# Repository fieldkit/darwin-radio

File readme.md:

DARWIN-RADIO

Experimental development repo for next-generation FieldKit hardware.

-- This hardware is experimental and still under development, the designs may contain errors. --

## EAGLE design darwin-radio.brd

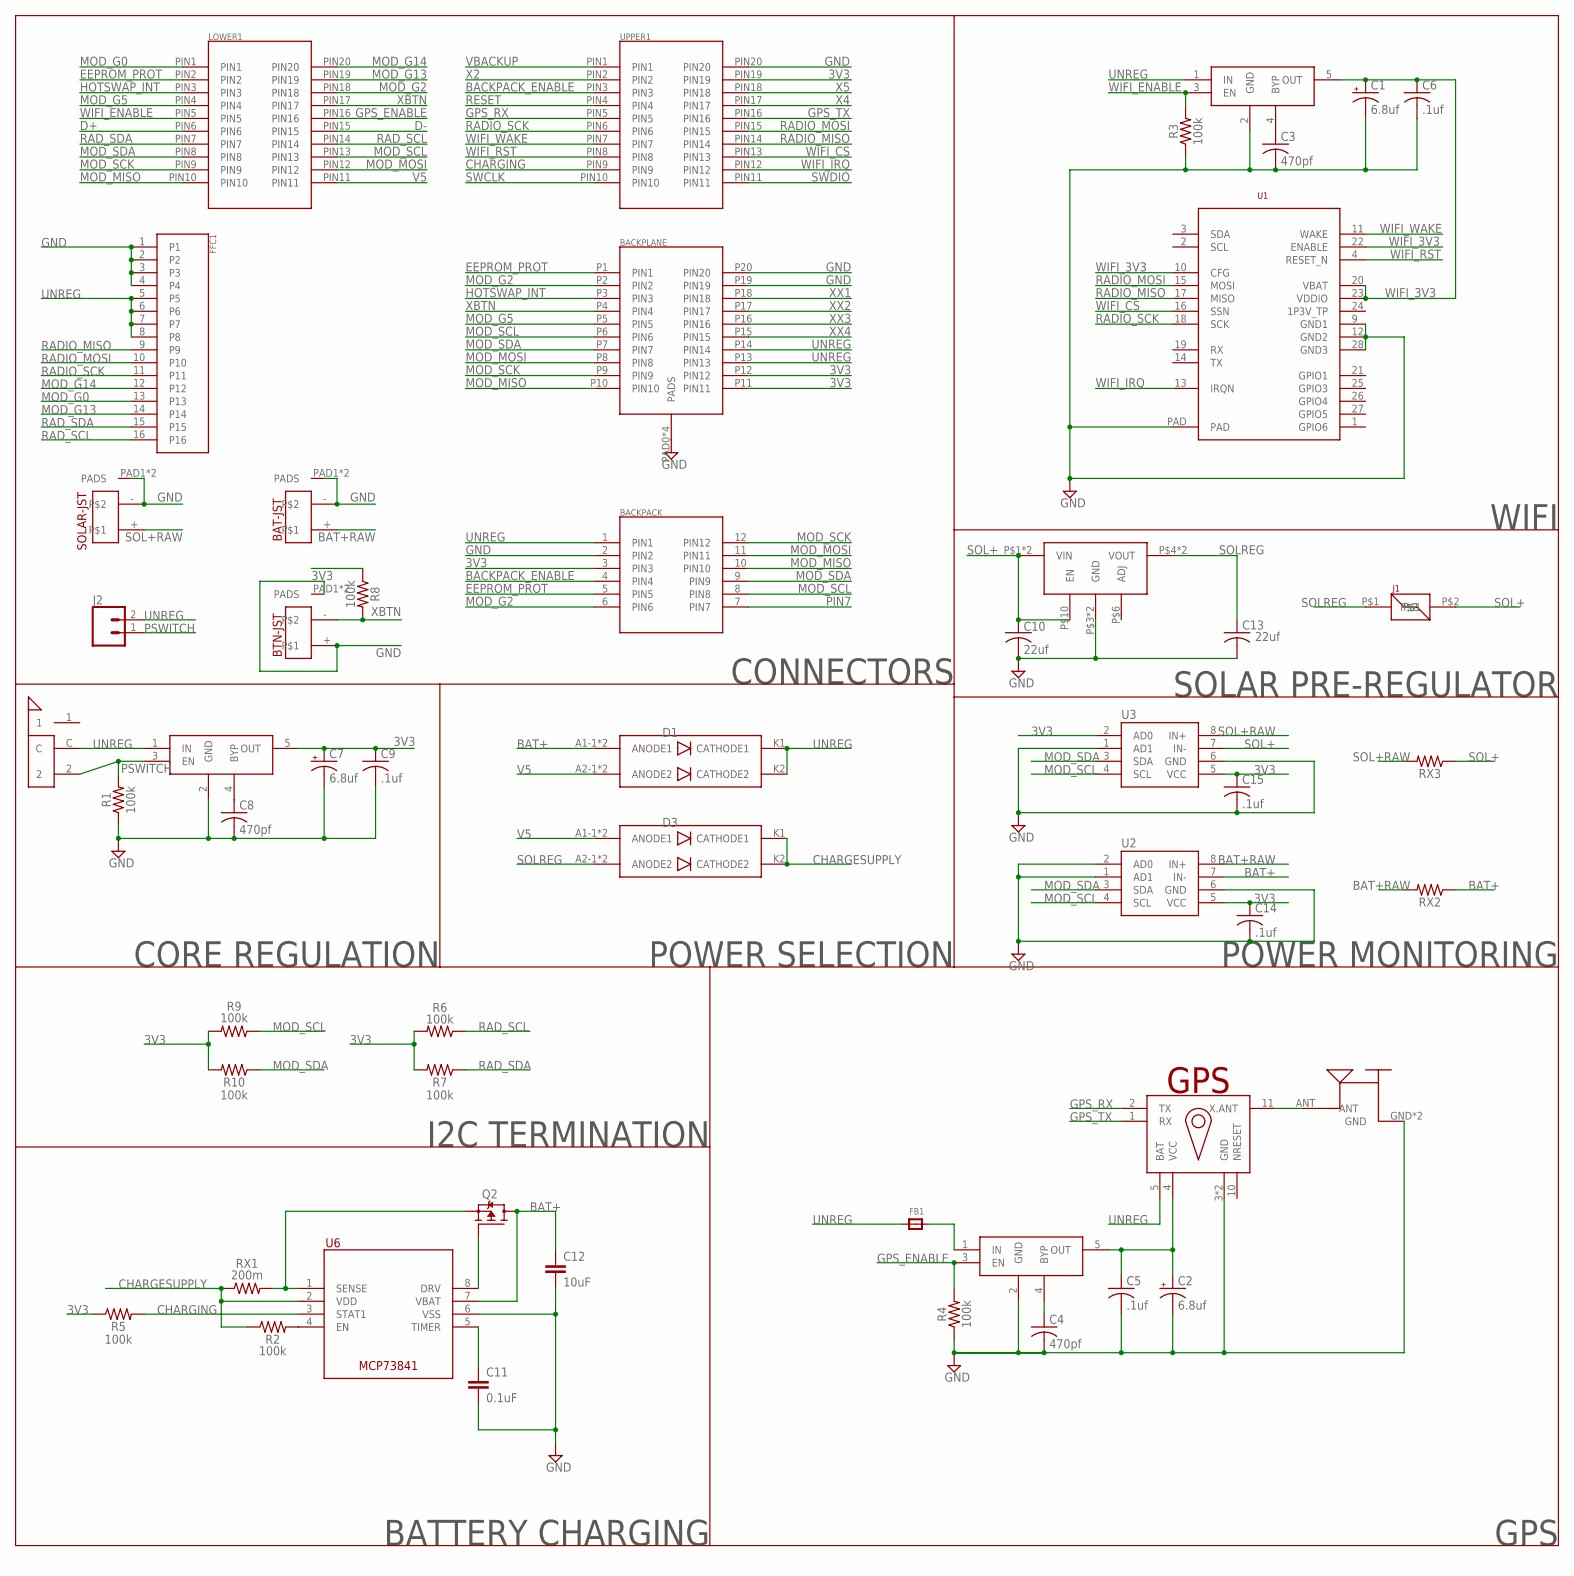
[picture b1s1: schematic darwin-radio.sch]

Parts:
BACKPACK: 2X6-HEADERSDS; 12PH
BACKPLANE: M55-6102042R
BAT-JST: B2B-PH-SM4-TB
BTN-JST: B2B-PH-SM4-TB
C1, C2, C7: 6.8uf; A/3216-18R
C3, C4, C8: 470pf; C0603K
C5, C6, C9, C14, C15: .1uf; C0603K
C10, C13: 22uf; C0603K
C11: 0.1uF; 0603
C12: 10uF; 0603
D1, D3: V10KL45DUHM3/H
FB1: FERRITE0805; 0805
FFC1: 505110-1692
J1: S1911-46R
J2: CONN_02LOCK_LONGPADS; 1X02_LOCK_LONGPADS
LOWER1: MOLEX-15-91-2200; 20PH
Q2: NDS8434; SO08-IRF
R1, R2, R3, R4, R5, R6, R7, R8, R9, R10: 100k; 0603
REG1: V78E06-1000-SMT-TR
RX1: 200m; R2512
RX2, RX3: 100M; R2512
SOLAR-JST: B2B-PH-SM4-TB
U1: ATWINC
U2, U3: INA219; SOIC127P599X175-8N
U6: MCP7384X; SOP65P490X110-8
U$1: FGPMMOPA6HL80; L80-M39
U$2, U$3, U$4: MIC5219-3.3YM5-TR; SOT95P280X145-5
U$5: SSAJ110100
U$11: 2337019-1
UPPER1: MOLEX-15-91-2200; 20PH

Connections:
3V3: BACKPACK.3 (PIN3), BACKPLANE.P11 (PIN11), BACKPLANE.P12 (PIN12), C7.+, C9.1, C14.1, C15.1, R5.1, R6.2, R7.2, R8.1, R9.2, R10.2, U2.5 (VCC), U3.2 (AD0), U3.5 (VCC), U$4.5 (OUT), UPPER1.PIN19
BACKPACK_ENABLE: BACKPACK.4 (PIN4), UPPER1.PIN3
BAT+: C12.1, D1.A1-1 (ANODE1), D1.A1-2 (ANODE1), Q2.5 (D), Q2.6 (D), Q2.7 (D), Q2.8 (D), RX2.1, U2.7 (IN-), U6.7 (VBAT)
BAT+RAW: BAT-JST.+, RX2.2, U2.8 (IN+)
CHARGESUPPLY: D3.K1 (CATHODE1), D3.K2 (CATHODE2), R2.1, RX1.1, U6.2 (VDD)
CHARGING: R5.2, U6.3 (STAT1), UPPER1.PIN9
D+: LOWER1.PIN6
D-: LOWER1.PIN15
EEPROM_PROT: BACKPACK.5 (PIN5), BACKPLANE.P1 (PIN1), LOWER1.PIN2
GND: BACKPACK.2 (PIN2), BACKPLANE.P19 (PIN19), BACKPLANE.P20 (PIN20), BACKPLANE.PAD0 (PADS), BACKPLANE.PAD1 (PADS), BACKPLANE.PAD2 (PADS), BACKPLANE.PAD3 (PADS), BAT-JST.-, BAT-JST.PAD1 (PADS), BAT-JST.PAD2 (PADS), BTN-JST.+, BTN-JST.PAD1 (PADS), BTN-JST.PAD2 (PADS), C1.-, C2.-, C3.2, C4.2, C5.2, C6.2, C7.-, C8.2, C9.2, C10.2, C11.2, C12.2, C13.2, C14.2, C15.2, FFC1.1, FFC1.2, FFC1.3, FFC1.4, R1.1, R3.1, R4.1, REG1.P$3 (GND), REG1.P$7 (GND), SOLAR-JST.-, SOLAR-JST.PAD1 (PADS), SOLAR-JST.PAD2 (PADS), U1.9 (GND1), U1.12 (GND2), U1.28 (GND3), U1.PAD, U2.1 (AD1), U2.2 (AD0), U2.6 (GND), U3.1 (AD1), U3.6 (GND), U6.6 (VSS), U$1.3 (GND), U$1.12 (GND), U$2.2 (GND), U$3.2 (GND), U$4.2 (GND), U$11.GND, U$11.GND2 (GND), UPPER1.PIN20
GPS_ENABLE: LOWER1.PIN16, R4.2, U$2.3 (EN)
GPS_RX: U$1.2 (TX), UPPER1.PIN5
GPS_TX: U$1.1 (RX), UPPER1.PIN16
HOTSWAP_INT: BACKPLANE.P3 (PIN3), LOWER1.PIN3
MOD_G0: FFC1.13, LOWER1.PIN1
MOD_G2: BACKPACK.6 (PIN6), BACKPLANE.P2 (PIN2), LOWER1.PIN18
MOD_G5: BACKPLANE.P5 (PIN5), LOWER1.PIN4
MOD_G13: FFC1.14, LOWER1.PIN19
MOD_G14: FFC1.12, LOWER1.PIN20
MOD_MISO: BACKPACK.10 (PIN10), BACKPLANE.P10 (PIN10), LOWER1.PIN10
MOD_MOSI: BACKPACK.11 (PIN11), BACKPLANE.P8 (PIN8), LOWER1.PIN12
MOD_SCK: BACKPACK.12 (PIN12), BACKPLANE.P9 (PIN9), LOWER1.PIN9
MOD_SCL: BACKPACK.8 (PIN8), BACKPLANE.P6 (PIN6), LOWER1.PIN13, R9.1, U2.4 (SCL), U3.4 (SCL)
MOD_SDA: BACKPACK.9 (PIN9), BACKPLANE.P7 (PIN7), LOWER1.PIN8, R10.1, U2.3 (SDA), U3.3 (SDA)
unnamed: C3.1, U$3.4 (BYP)
unnamed: C4.1, U$2.4 (BYP)
unnamed: C2.+, C5.1, U$1.4 (VCC), U$2.5 (OUT)
unnamed: U$1.11 (X.ANT), U$11.ANT
unnamed: R2.2, U6.4 (EN)
unnamed: C8.1, U$4.4 (BYP)
unnamed: FB1.2, U$2.1 (IN)
unnamed: Q2.1 (S), Q2.2 (S), Q2.3 (S), RX1.2, U6.1 (SENSE)
unnamed: Q2.4 (G), U6.8 (DRV)
unnamed: C11.1, U6.5 (TIMER)
PIN7: BACKPACK.7 (PIN7)
PSWITCH: J2.1, R1.2, U$4.3 (EN), U$5.2
RADIO_MISO: FFC1.9, U1.17 (MISO), UPPER1.PIN14
RADIO_MOSI: FFC1.10, U1.15 (MOSI), UPPER1.PIN15
RADIO_SCK: FFC1.11, U1.18 (SCK), UPPER1.PIN6
RAD_SCL: FFC1.16, LOWER1.PIN14, R6.1
RAD_SDA: FFC1.15, LOWER1.PIN7, R7.1
RESET: UPPER1.PIN4
SOL+: C10.1, J1.P$2, REG1.P$1 (VIN), REG1.P$2 (VIN), REG1.P$10 (EN), RX3.1, U3.7 (IN-)
SOL+RAW: RX3.2, SOLAR-JST.+, U3.8 (IN+)
SOLREG: C13.1, D3.A2-1 (ANODE2), D3.A2-2 (ANODE2), J1.P$1, REG1.P$4 (VOUT), REG1.P$5 (VOUT)
SWCLK: UPPER1.PIN10
SWDIO: UPPER1.PIN11
UNREG: BACKPACK.1 (PIN1), BACKPLANE.P13 (PIN13), BACKPLANE.P14 (PIN14), D1.K1 (CATHODE1), D1.K2 (CATHODE2), FB1.1, FFC1.5, FFC1.6, FFC1.7, FFC1.8, J2.2, U$1.5 (BAT), U$3.1 (IN), U$4.1 (IN), U$5.C
V5: D1.A2-1 (ANODE2), D1.A2-2 (ANODE2), D3.A1-1 (ANODE1), D3.A1-2 (ANODE1), LOWER1.PIN11
VBACKUP: UPPER1.PIN1
WIFI_3V3: C1.+, C6.1, U1.10 (CFG), U1.20 (VBAT), U1.22 (ENABLE), U1.23 (VDDIO), U$3.5 (OUT)
WIFI_CS: U1.16 (SSN), UPPER1.PIN13
WIFI_ENABLE: LOWER1.PIN5, R3.2, U$3.3 (EN)
WIFI_IRQ: U1.13 (IRQN), UPPER1.PIN12
WIFI_RST: U1.4 (RESET_N), UPPER1.PIN8
WIFI_WAKE: U1.11 (WAKE), UPPER1.PIN7
X2: UPPER1.PIN2
X4: UPPER1.PIN17
X5: UPPER1.PIN18
XBTN: BACKPLANE.P4 (PIN4), BTN-JST.-, LOWER1.PIN17, R8.2
XX1: BACKPLANE.P18 (PIN18)
XX2: BACKPLANE.P17 (PIN17)
XX3: BACKPLANE.P16 (PIN16)
XX4: BACKPLANE.P15 (PIN15)

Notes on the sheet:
BATTERY CHARGING
POWER MONITORING
WIFI
POWER SELECTION
CORE REGULATION
CONNECTORS
GPS
I2C TERMINATION
SOLAR PRE-REGULATOR

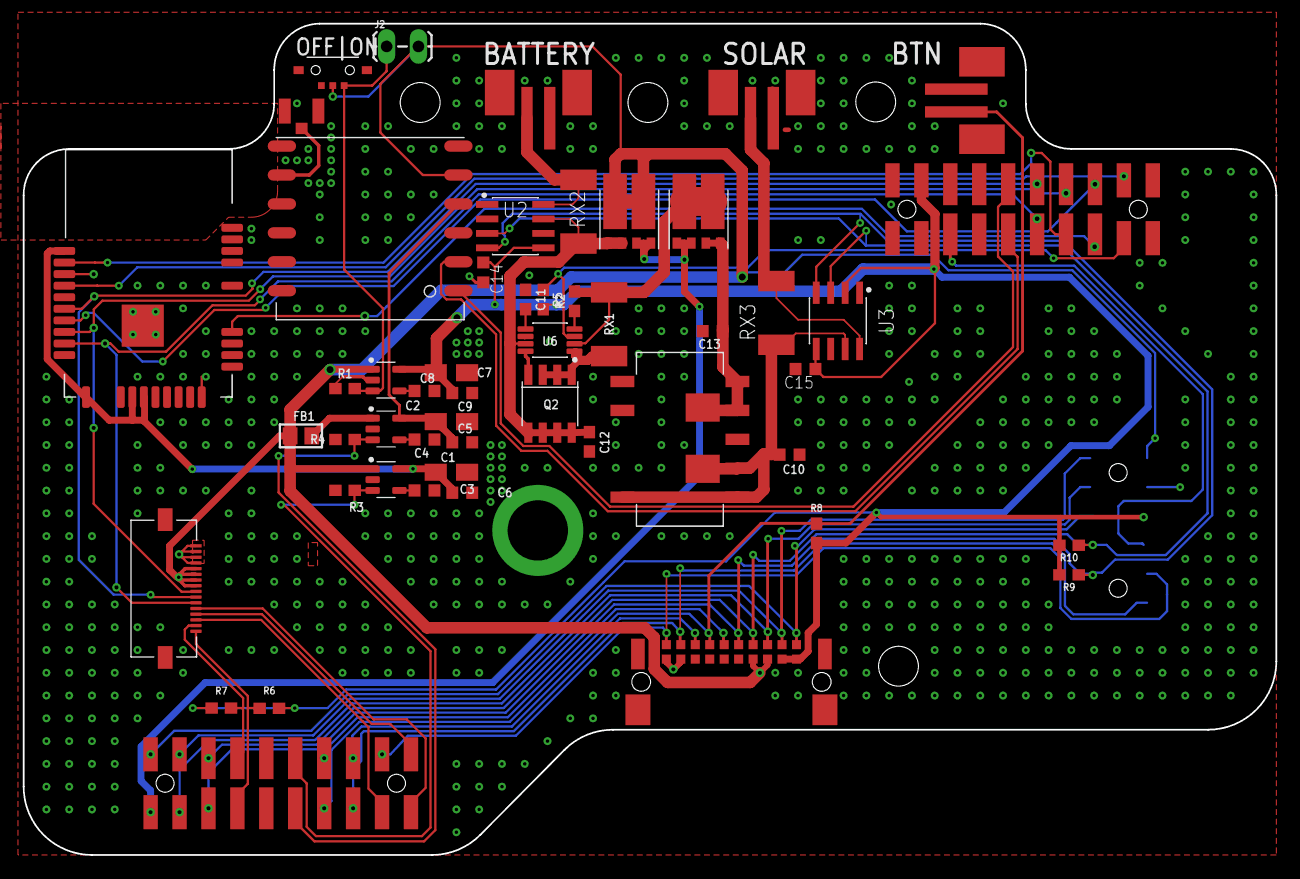
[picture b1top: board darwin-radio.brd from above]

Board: 2 copper layers, 110.0 x 73.0 mm, 53 parts (1 on the bottom side), 50 nets.

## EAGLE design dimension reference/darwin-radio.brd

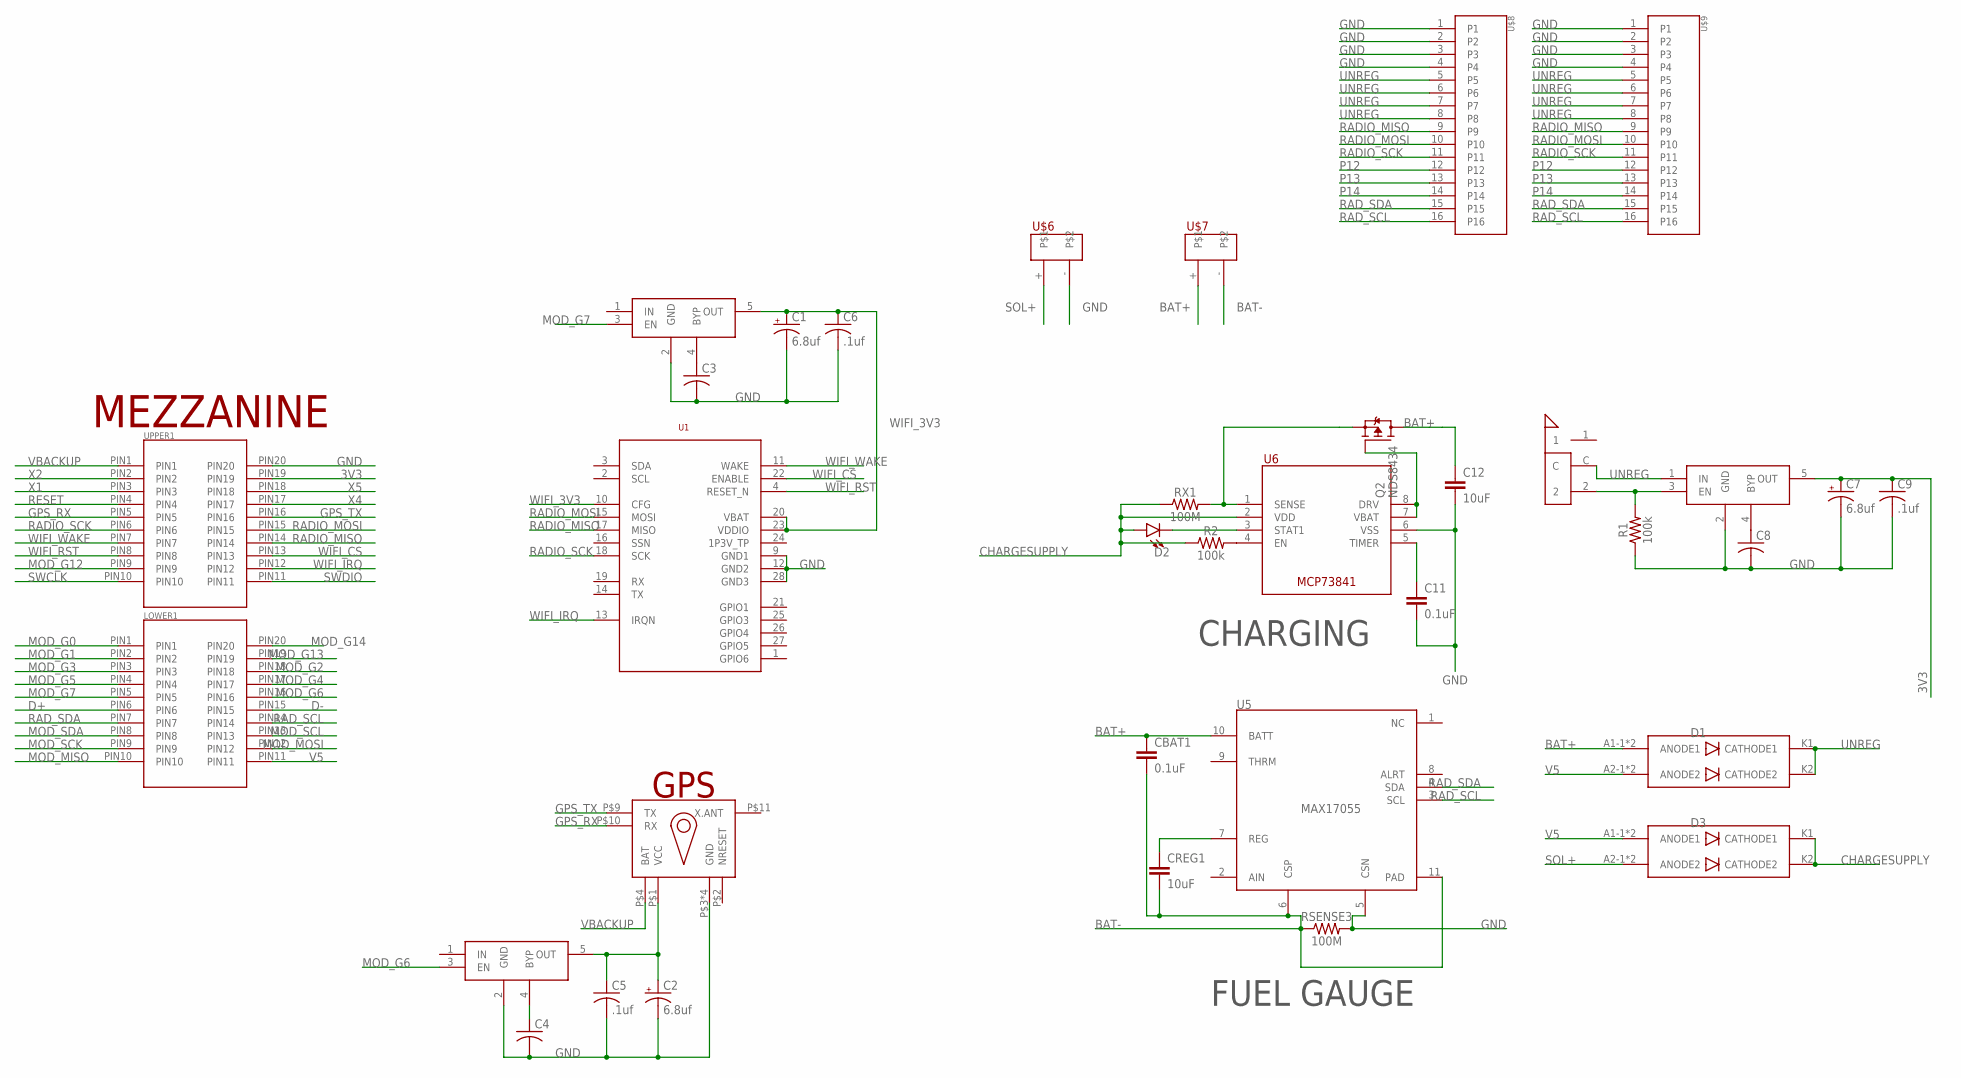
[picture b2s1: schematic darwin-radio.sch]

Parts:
C1, C2, C7: 6.8uf; A/3216-18R
C3, C4, C8: C-USC0603K; C0603K
C5, C6, C9: .1uf; C0603K
C11: 0.1uF; 0603
C12: 10uF; 0603
CBAT1: 0.1uF; 0603
CREG1: 10uF; 0603
D1, D3: V10KL45DUHM3/H
D2: LED0603; LED-0603
LOWER1: MOLEX-15-91-2200; 20PH
Q2: NDS8434; SO08-IRF
R1, R2: 100k; 0603
RSENSE3: 100M; 0603
RX1: 100M; 0603
U1: ATWINC
U5: MAX17055; SON50P300X300X75-11T150X230
U6: MCP7384X; SOP65P490X110-8
U$1: FGPMMOPA6H; GPS_MODULE
U$2, U$3, U$4: MIC5219-3.3YM5-TR; SOT95P280X145-5
U$5: SSAJ110100
U$6, U$7: B2B-PH-SM4-TB
U$8, U$9: 505110-1692
UPPER1: MOLEX-15-91-2200; 20PH

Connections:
3V3: C7.+, C9.1, U$4.5 (OUT), UPPER1.PIN19
BAT+: C12.1, CBAT1.1, D1.A1-1 (ANODE1), D1.A1-2 (ANODE1), Q2.5 (D), Q2.6 (D), Q2.7 (D), Q2.8 (D), U5.10 (BATT), U$7.+
BAT-: CBAT1.2, CREG1.2, RSENSE3.1, U5.6 (CSP), U5.11 (PAD), U$7.-
CHARGESUPPLY: D2.A, D3.K1 (CATHODE1), D3.K2 (CATHODE2), R2.1, RX1.1, U6.2 (VDD)
D+: LOWER1.PIN6
D-: LOWER1.PIN15
GND: C1.-, C2.-, C3.2, C4.2, C5.2, C6.2, C7.-, C8.2, C9.2, C11.2, C12.2, R1.1, RSENSE3.2, U1.9 (GND1), U1.12 (GND2), U1.28 (GND3), U5.5 (CSN), U6.6 (VSS), U$1.P$3 (GND), U$1.P$8 (GND), U$1.P$12 (GND), U$1.P$19 (GND), U$2.2 (GND), U$3.2 (GND), U$4.2 (GND), U$6.-, U$8.1, U$8.2, U$8.3, U$8.4, U$9.1, U$9.2, U$9.3, U$9.4, UPPER1.PIN20
GPS_RX: U$1.P$10 (RX), UPPER1.PIN5
GPS_TX: U$1.P$9 (TX), UPPER1.PIN16
MOD_G0: LOWER1.PIN1
MOD_G1: LOWER1.PIN2
MOD_G2: LOWER1.PIN18
MOD_G3: LOWER1.PIN3
MOD_G4: LOWER1.PIN17
MOD_G5: LOWER1.PIN4
MOD_G6: LOWER1.PIN16, U$2.3 (EN)
MOD_G7: LOWER1.PIN5, U$3.3 (EN)
MOD_G12: UPPER1.PIN9
MOD_G13: LOWER1.PIN19
MOD_G14: LOWER1.PIN20
MOD_MISO: LOWER1.PIN10
MOD_MOSI: LOWER1.PIN12
MOD_SCK: LOWER1.PIN9
MOD_SCL: LOWER1.PIN13
MOD_SDA: LOWER1.PIN8
unnamed: C3.1, U$3.4 (BYP)
unnamed: C4.1, U$2.4 (BYP)
unnamed: C2.+, C5.1, U$1.P$1 (VCC), U$2.5 (OUT)
unnamed: R2.2, U6.4 (EN)
unnamed: C8.1, U$4.4 (BYP)
unnamed: R1.2, U$4.3 (EN), U$5.2
unnamed: Q2.1 (S), Q2.2 (S), Q2.3 (S), RX1.2, U6.1 (SENSE)
unnamed: D2.C, U6.3 (STAT1)
unnamed: Q2.4 (G), U6.7 (VBAT), U6.8 (DRV)
unnamed: C11.1, U6.5 (TIMER)
unnamed: CREG1.1, U5.7 (REG)
P12: U$8.12, U$9.12
P13: U$8.13, U$9.13
P14: U$8.14, U$9.14
RADIO_MISO: U1.17 (MISO), U$8.9, U$9.9, UPPER1.PIN14
RADIO_MOSI: U1.15 (MOSI), U$8.10, U$9.10, UPPER1.PIN15
RADIO_SCK: U1.18 (SCK), U$8.11, U$9.11, UPPER1.PIN6
RAD_SCL: LOWER1.PIN14, U5.3 (SCL), U$8.16, U$9.16
RAD_SDA: LOWER1.PIN7, U5.4 (SDA), U$8.15, U$9.15
RESET: UPPER1.PIN4
SOL+: D3.A2-1 (ANODE2), D3.A2-2 (ANODE2), U$6.+
SWCLK: UPPER1.PIN10
SWDIO: UPPER1.PIN11
UNREG: D1.K1 (CATHODE1), D1.K2 (CATHODE2), U$4.1 (IN), U$5.C, U$8.5, U$8.6, U$8.7, U$8.8, U$9.5, U$9.6, U$9.7, U$9.8
V5: D1.A2-1 (ANODE2), D1.A2-2 (ANODE2), D3.A1-1 (ANODE1), D3.A1-2 (ANODE1), LOWER1.PIN11
VBACKUP: U$1.P$4 (BAT), UPPER1.PIN1
WIFI_3V3: C1.+, C6.1, U1.10 (CFG), U1.20 (VBAT), U1.23 (VDDIO), U$3.5 (OUT)
WIFI_CS: U1.22 (ENABLE), UPPER1.PIN13
WIFI_IRQ: U1.13 (IRQN), UPPER1.PIN12
WIFI_RST: U1.4 (RESET_N), UPPER1.PIN8
WIFI_WAKE: U1.11 (WAKE), UPPER1.PIN7
X1: UPPER1.PIN3
X2: UPPER1.PIN2
X4: UPPER1.PIN17
X5: UPPER1.PIN18

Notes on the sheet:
MEZZANINE
CHARGING
FUEL GAUGE

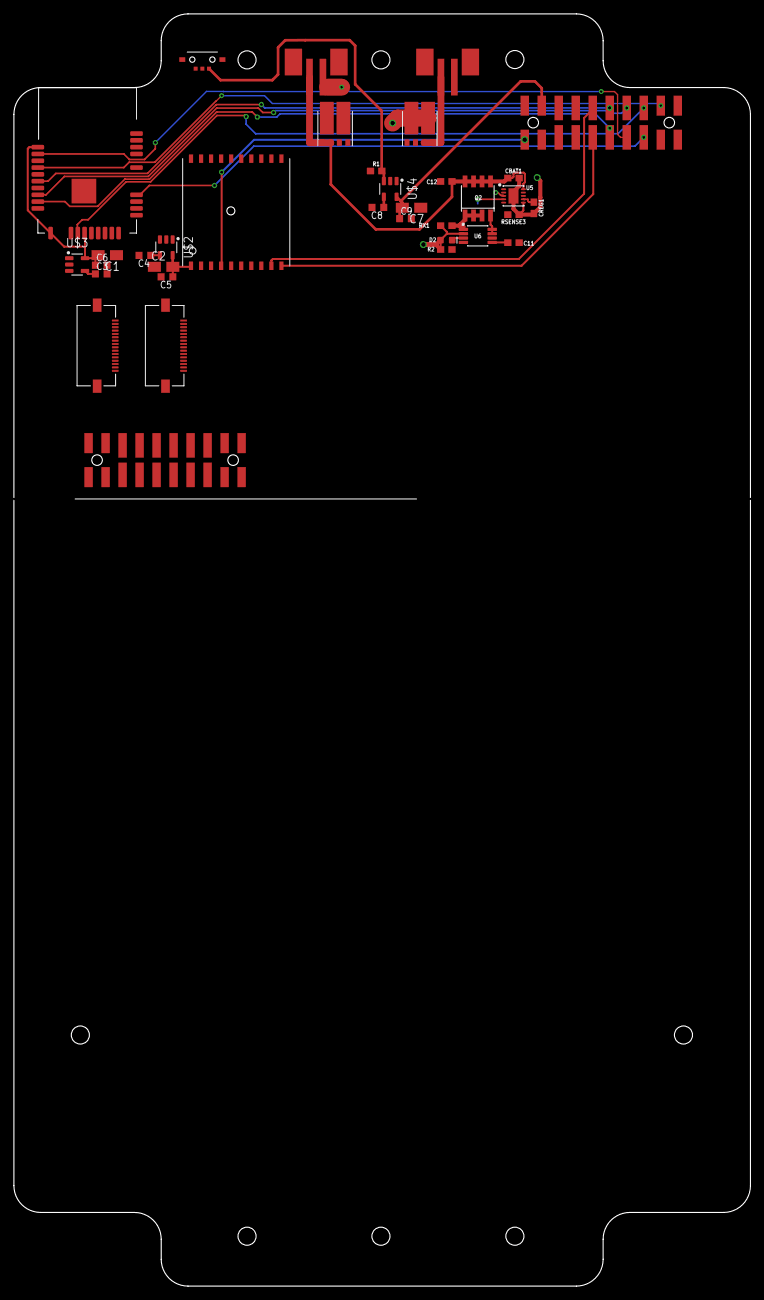
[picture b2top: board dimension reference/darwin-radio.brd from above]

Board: 4 copper layers, 110.0 x 190.0 mm, 35 parts (0 on the bottom side), 37 nets.

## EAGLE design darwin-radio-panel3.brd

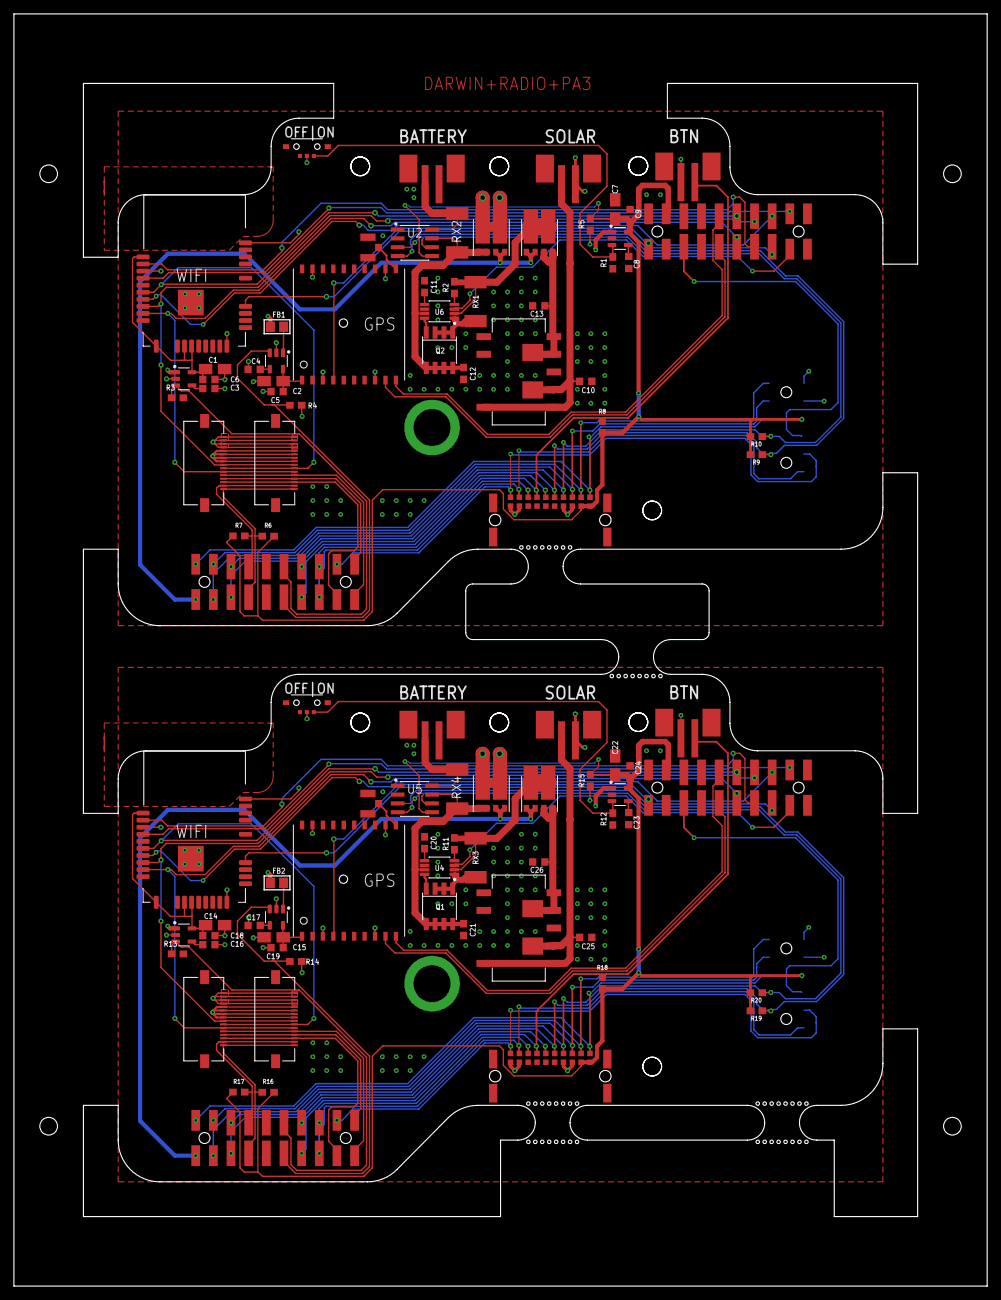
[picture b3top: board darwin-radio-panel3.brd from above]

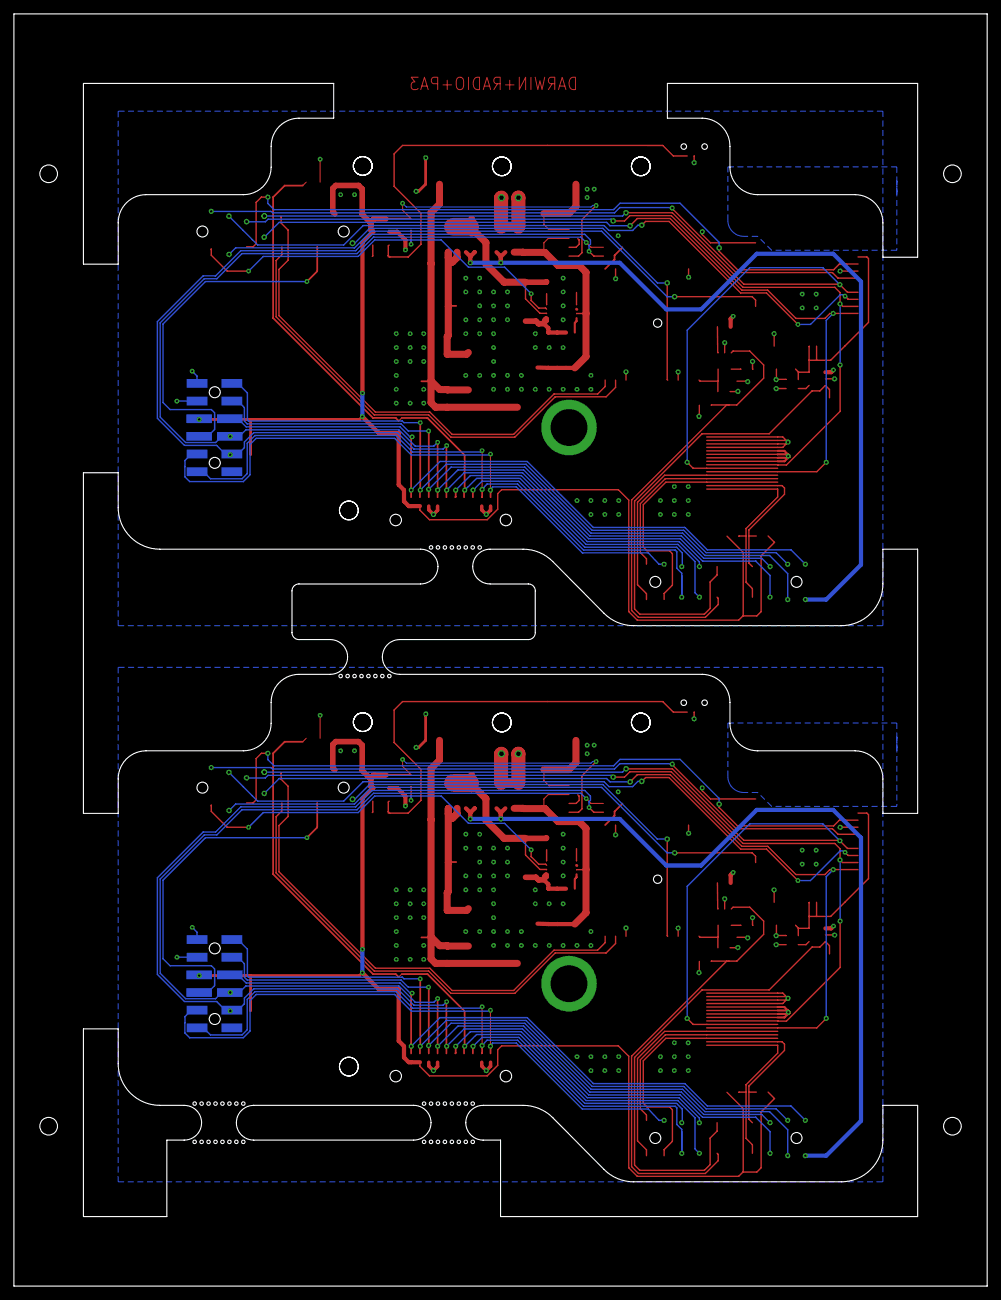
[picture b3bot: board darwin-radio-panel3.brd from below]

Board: 4 copper layers, 140.0 x 183.0 mm, 98 parts (2 on the bottom side), 100 nets.

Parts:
BACKPACK, BACKPACK1: 2X6-HEADERSDS; 12PH
BACKPLANE, BACKPLANE1: M55-6102042R
BAT-JST, BAT-JST1: B2B-PH-SM4-TB
BTN-JST, BTN-JST1: B2B-PH-SM4-TB
C1, C2, C7, C14, C15, C22: 6.8uf; A/3216-18R
C3, C4, C8, C16, C17, C23: 470pf; C0603K
C5, C6, C9, C18, C19, C24: .1uf; C0603K
C10, C13, C25, C26: 22uf; C0603K
C11, C20: 0.1uF; 0603
C12, C21: 10uF; 0603
D1, D2, D3, D4: V10KL45DUHM3/H
FB1, FB2: 0805
FFC1, FFC2, FFC3, FFC4: 505110-1692
J1, J2: S1911-46R
LOWER1, LOWER2: MOLEX-15-91-2200; 20PH
Q1, Q2: NDS8434; SO08-IRF
R1, R2, R3, R4, R5, R6, R7, R8, R9, R10, R11, R12, R13, R14, R15, R16, R17, R18, R19, R20: 100k; 0603
REG1, REG2: V78E06-1000-SMT-TR
RX1, RX2, RX3, RX4: 100M; R2512
SOLAR-JST, SOLAR-JST1: B2B-PH-SM4-TB
U1, U3: ATWINC
U2, U5: INA219; SOIC127P599X175-8N
U4, U6: MCP7384X; SOP65P490X110-8
U$1, U$6: FGPMMOPA6H; GPS_MODULE
U$2, U$3, U$4, U$7, U$8, U$9: MIC5219-3.3YM5-TR; SOT95P280X145-5
U$5, U$10: SSAJ110100
U$11, U$12: 2337019-1
UPPER1, UPPER2: MOLEX-15-91-2200; 20PH

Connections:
3V1: BACKPACK1.3, BACKPLANE1.P11, BACKPLANE1.P12, C22.+, C24.1, R15.1, R16.2, R17.2, R18.1, R19.2, R20.2, U5.5, U$9.5, UPPER2.PIN19
3V3: BACKPACK.3, BACKPLANE.P11, BACKPLANE.P12, C7.+, C9.1, R5.1, R6.2, R7.2, R8.1, R9.2, R10.2, U2.5, U$4.5, UPPER1.PIN19
BACKPACK_ENABLE: BACKPACK.4, UPPER1.PIN3
BACKPACK_ENABLE1: BACKPACK1.4, UPPER2.PIN3
BAT+: C12.1, D1.A1-1, D1.A1-2, Q2.5, Q2.6, Q2.7, Q2.8, RX2.1, U2.7, U6.7
BAT+1: C21.1, D2.A1-1, D2.A1-2, Q1.5, Q1.6, Q1.7, Q1.8, RX4.1, U4.7, U5.7
BAT+RAW: BAT-JST.+, RX2.2, U2.8
BAT+RAW1: BAT-JST1.+, RX4.2, U5.8
CHARGESUPPLY: D3.K1, D3.K2, R2.1, RX1.1, U6.2
CHARGESUPPLY1: D4.K1, D4.K2, R11.1, RX3.1, U4.2
CHARGING: R5.2, U6.3, UPPER1.PIN9
CHARGING1: R15.2, U4.3, UPPER2.PIN9
EEPROM_PROT: BACKPACK.5, BACKPLANE.P1, LOWER1.PIN2
EEPROM_PROT1: BACKPACK1.5, BACKPLANE1.P1, LOWER2.PIN2
GND: BACKPACK.2, BACKPLANE.P19, BACKPLANE.P20, BAT-JST.-, BTN-JST.+, C1.-, C2.-, C3.2, C4.2, C5.2, C6.2, C7.-, C8.2, C9.2, C10.2, C11.2, C12.2, C13.2, FFC1.1, FFC1.2, FFC1.3, FFC1.4, FFC2.1, FFC2.2, FFC2.3, FFC2.4, R1.1, R3.1, R4.1, REG1.P$3, REG1.P$7, SOLAR-JST.-, U1.9, U1.12, U1.28, U1.PAD, U2.1, U2.2, U2.6, U6.6, U$1.P$3, U$1.P$8, U$1.P$12, U$1.P$19, U$2.2, U$3.2, U$4.2, U$11.GND, U$11.GND2, UPPER1.PIN20
GND2: BACKPACK1.2, BACKPLANE1.P19, BACKPLANE1.P20, BAT-JST1.-, BTN-JST1.+, C14.-, C15.-, C16.2, C17.2, C18.2, C19.2, C20.2, C21.2, C22.-, C23.2, C24.2, C25.2, C26.2, FFC3.1, FFC3.2, FFC3.3, FFC3.4, FFC4.1, FFC4.2, FFC4.3, FFC4.4, R12.1, R13.1, R14.1, REG2.P$3, REG2.P$7, SOLAR-JST1.-, U3.9, U3.12, U3.28, U3.PAD, U4.6, U5.1, U5.2, U5.6, U$6.P$3, U$6.P$8, U$6.P$12, U$6.P$19, U$7.2, U$8.2, U$9.2, U$12.GND, U$12.GND2, UPPER2.PIN20
GPS_ENABLE: LOWER1.PIN16, R4.2, U$2.3
GPS_ENABLE1: LOWER2.PIN16, R14.2, U$7.3
GPS_RX: U$1.P$9, UPPER1.PIN5
GPS_RX1: U$6.P$9, UPPER2.PIN5
GPS_TX: U$1.P$10, UPPER1.PIN16
GPS_TX1: U$6.P$10, UPPER2.PIN16
HOTSWAP_INT: BACKPLANE.P3, LOWER1.PIN3
HOTSWAP_INT1: BACKPLANE1.P3, LOWER2.PIN3
MOD_G0: FFC1.13, FFC2.13, LOWER1.PIN1
MOD_G1: FFC3.13, FFC4.13, LOWER2.PIN1
MOD_G2: BACKPACK.6, BACKPLANE.P2, LOWER1.PIN18
MOD_G3: BACKPACK1.6, BACKPLANE1.P2, LOWER2.PIN18
MOD_G4: BACKPLANE1.P5, LOWER2.PIN4
MOD_G5: BACKPLANE.P5, LOWER1.PIN4
MOD_G6: FFC3.14, FFC4.14, LOWER2.PIN19
MOD_G7: FFC3.12, FFC4.12, LOWER2.PIN20
MOD_G13: FFC1.14, FFC2.14, LOWER1.PIN19
MOD_G14: FFC1.12, FFC2.12, LOWER1.PIN20
MOD_MISO: BACKPACK.10, BACKPLANE.P10, LOWER1.PIN10
MOD_MISO1: BACKPACK1.10, BACKPLANE1.P10, LOWER2.PIN10
MOD_MOSI: BACKPACK.11, BACKPLANE.P8, LOWER1.PIN12
MOD_MOSI1: BACKPACK1.11, BACKPLANE1.P8, LOWER2.PIN12
MOD_SCK: BACKPACK.12, BACKPLANE.P9, LOWER1.PIN9
MOD_SCK1: BACKPACK1.12, BACKPLANE1.P9, LOWER2.PIN9
MOD_SCL: BACKPACK.8, BACKPLANE.P6, LOWER1.PIN13, R9.1, U2.4
MOD_SCL1: BACKPACK1.8, BACKPLANE1.P6, LOWER2.PIN13, R19.1, U5.4
MOD_SDA: BACKPACK.9, BACKPLANE.P7, LOWER1.PIN8, R10.1, U2.3
MOD_SDA1: BACKPACK1.9, BACKPLANE1.P7, LOWER2.PIN8, R20.1, U5.3
unnamed: C3.1, U$3.4
unnamed: C4.1, U$2.4
unnamed: C2.+, C5.1, U$1.P$1, U$2.5
unnamed: U$1.P$11, U$11.ANT
unnamed: R2.2, U6.4
unnamed: C8.1, U$4.4
unnamed: FB1.2, U$2.1
unnamed: R1.2, U$4.3, U$5.2
unnamed: C16.1, U$8.4
unnamed: C17.1, U$7.4
unnamed: C15.+, C19.1, U$6.P$1, U$7.5
unnamed: Q2.1, Q2.2, Q2.3, RX1.2, U6.1
unnamed: Q1.1, Q1.2, Q1.3, RX3.2, U4.1
unnamed: Q2.4, U6.8
unnamed: C11.1, U6.5
unnamed: Q1.4, U4.8
unnamed: C20.1, U4.5
unnamed: R11.2, U4.4
unnamed: C23.1, U$9.4
unnamed: R12.2, U$9.3, U$10.2
unnamed: U$6.P$11, U$12.ANT
unnamed: FB2.2, U$7.1
RADIO_MISO: FFC1.9, FFC2.9, U1.17, UPPER1.PIN14
RADIO_MISO1: FFC3.9, FFC4.9, U3.17, UPPER2.PIN14
RADIO_MOSI: FFC1.10, FFC2.10, U1.15, UPPER1.PIN15
RADIO_MOSI1: FFC3.10, FFC4.10, U3.15, UPPER2.PIN15
RADIO_SCK: FFC1.11, FFC2.11, U1.18, UPPER1.PIN6
RADIO_SCK1: FFC3.11, FFC4.11, U3.18, UPPER2.PIN6
RAD_SCL: FFC1.16, FFC2.16, LOWER1.PIN14, R6.1
RAD_SCL1: FFC3.16, FFC4.16, LOWER2.PIN14, R16.1
RAD_SDA: FFC1.15, FFC2.15, LOWER1.PIN7, R7.1
RAD_SDA1: FFC3.15, FFC4.15, LOWER2.PIN7, R17.1
SOL+: C10.1, J1.P$2, REG1.P$1, REG1.P$2, REG1.P$10, SOLAR-JST.+
SOL+1: C25.1, J2.P$2, REG2.P$1, REG2.P$2, REG2.P$10, SOLAR-JST1.+
SOLREG: C13.1, D3.A2-1, D3.A2-2, J1.P$1, REG1.P$4, REG1.P$5
SOLREG1: C26.1, D4.A2-1, D4.A2-2, J2.P$1, REG2.P$4, REG2.P$5
UNREG: BACKPACK.1, BACKPLANE.P13, BACKPLANE.P14, D1.K1, D1.K2, FB1.1, FFC1.5, FFC1.6, FFC1.7, FFC1.8, FFC2.5, FFC2.6, FFC2.7, FFC2.8, U$3.1, U$4.1, U$5.C
UNREG1: BACKPACK1.1, BACKPLANE1.P13, BACKPLANE1.P14, D2.K1, D2.K2, FB2.1, FFC3.5, FFC3.6, FFC3.7, FFC3.8, FFC4.5, FFC4.6, FFC4.7, FFC4.8, U$8.1, U$9.1, U$10.C
V1: D2.A2-1, D2.A2-2, D4.A1-1, D4.A1-2, LOWER2.PIN11
V5: D1.A2-1, D1.A2-2, D3.A1-1, D3.A1-2, LOWER1.PIN11
VBACKUP: U$1.P$4, UPPER1.PIN1
VBACKUP1: U$6.P$4, UPPER2.PIN1
WIFI_3V1: C14.+, C18.1, U3.10, U3.20, U3.22, U3.23, U$8.5
WIFI_3V3: C1.+, C6.1, U1.10, U1.20, U1.22, U1.23, U$3.5
WIFI_CS: U1.16, UPPER1.PIN13
WIFI_CS1: U3.16, UPPER2.PIN13
WIFI_ENABLE: LOWER1.PIN5, R3.2, U$3.3
WIFI_ENABLE1: LOWER2.PIN5, R13.2, U$8.3
WIFI_IRQ: U1.13, UPPER1.PIN12
WIFI_IRQ1: U3.13, UPPER2.PIN12
WIFI_RST: U1.4, UPPER1.PIN8
WIFI_RST1: U3.4, UPPER2.PIN8
WIFI_WAKE: U1.11, UPPER1.PIN7
WIFI_WAKE1: U3.11, UPPER2.PIN7
XBTN: BACKPLANE.P4, BTN-JST.-, LOWER1.PIN17, R8.2
XBTN1: BACKPLANE1.P4, BTN-JST1.-, LOWER2.PIN17, R18.2

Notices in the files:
parts and their libraries:
SparkFun-Resistors: Licensing: Creative Commons ShareAlike 4.0 International - https://creativecommons.org/licenses/by-sa/4.0
